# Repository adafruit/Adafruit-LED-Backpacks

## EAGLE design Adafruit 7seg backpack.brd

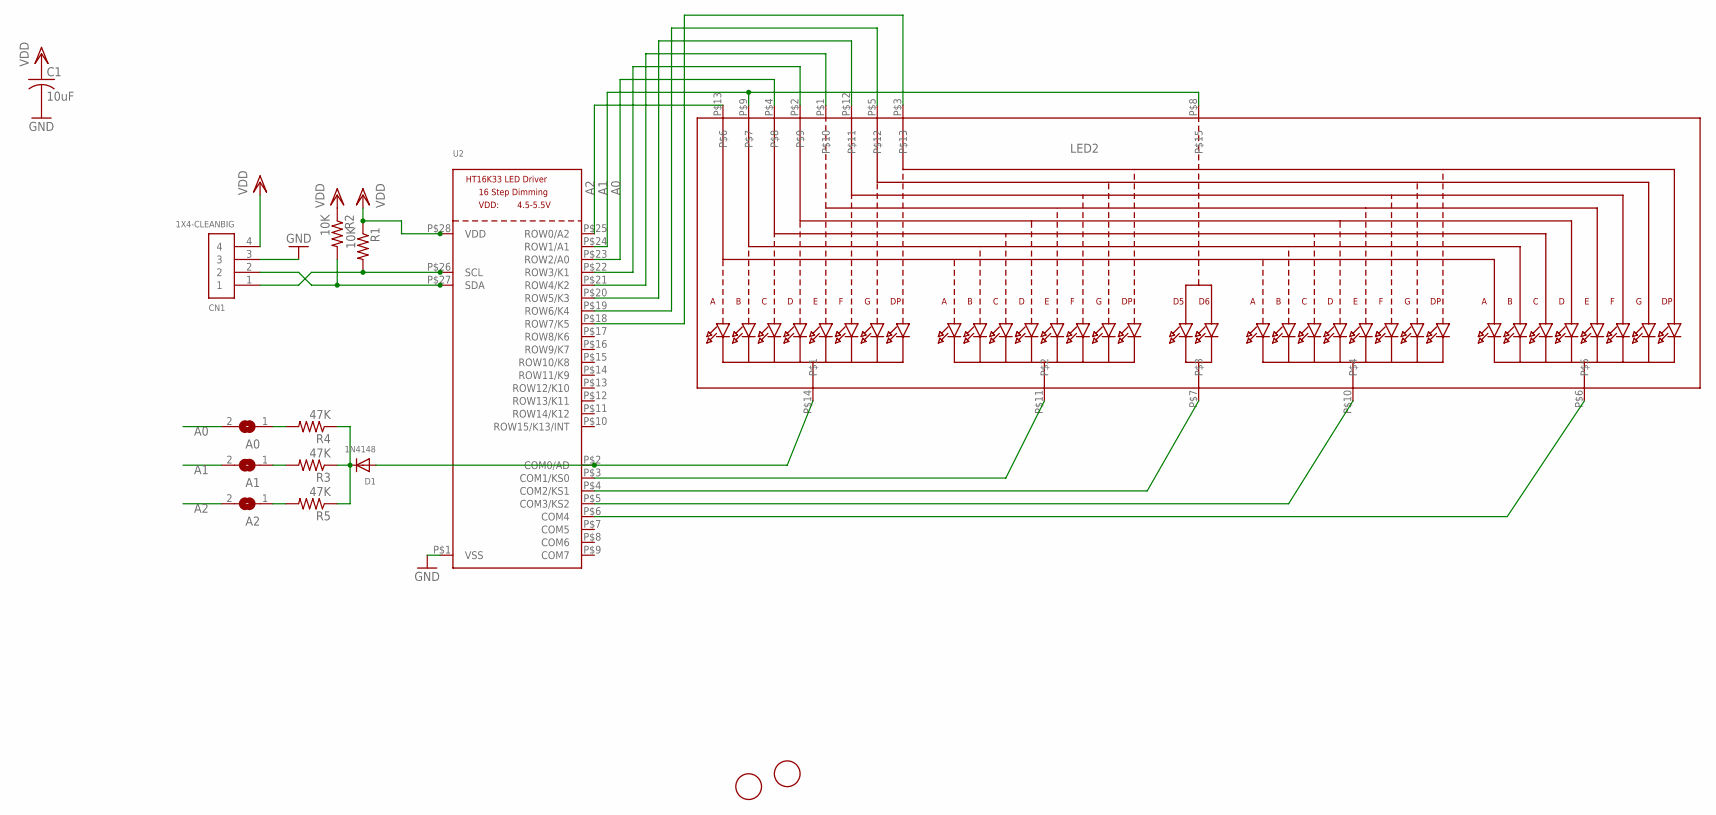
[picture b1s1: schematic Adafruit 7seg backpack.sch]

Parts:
A0, A1, A2: SOLDERJUMPERREFLOW_NOPASTE; SOLDERJUMPER_REFLOW_NOPASTE
C1: 10uF; C0805K
CN1: 1X4-CLEANBIG; 1X04-CLEANBIG
D1: 1N4148; SOD-323F
LED2: DISP_SEGMENT_4DIGIT_BL-Q56C43; SEGMENT-BL-Q56C43
R1, R2: 10K; R0805
R3, R4, R5: 47K; R0805
U2: HT16K33_SOP28; SOP28_300MIL
U$1, U$2: FIDUCIAL; FIDUCIAL_1MM

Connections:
A0: A0.2, LED2.P$4, U2.P$23 (ROW2/A0)
A1: A1.2, LED2.P$8, LED2.P$9, U2.P$24 (ROW1/A1)
A2: A2.2, LED2.P$13, U2.P$25 (ROW0/A2)
GND: C1.2, CN1.3, U2.P$1 (VSS)
unnamed: D1.C, R3.1, R4.1, R5.1
unnamed: D1.A, LED2.P$14, U2.P$2 (COM0/AD)
unnamed: LED2.P$11, U2.P$3 (COM1/KS0)
unnamed: LED2.P$7, U2.P$4 (COM2/KS1)
unnamed: LED2.P$10, U2.P$5 (COM3/KS2)
unnamed: LED2.P$6, U2.P$6 (COM4)
unnamed: A2.1, R5.2
unnamed: LED2.P$2, U2.P$22 (ROW3/K1)
unnamed: LED2.P$1, U2.P$21 (ROW4/K2)
unnamed: LED2.P$12, U2.P$20 (ROW5/K3)
unnamed: LED2.P$5, U2.P$19 (ROW6/K4)
unnamed: LED2.P$3, U2.P$18 (ROW7/K5)
unnamed: A1.1, R3.2
unnamed: A0.1, R4.2
SCL: CN1.1, R1.2, U2.P$26 (SCL)
SDA: CN1.2, R2.2, U2.P$27 (SDA)
VDD: C1.1, CN1.4, R1.1, R2.1, U2.P$28 (VDD)

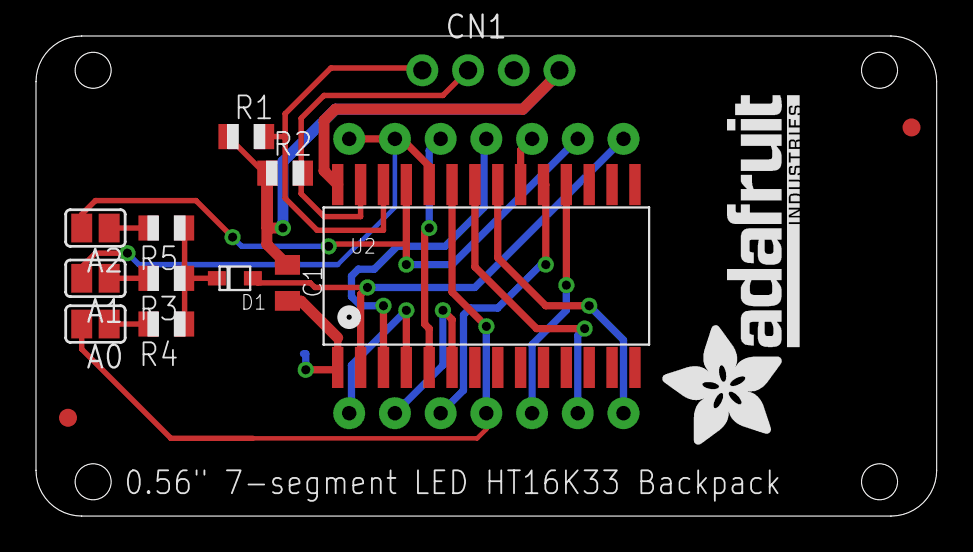
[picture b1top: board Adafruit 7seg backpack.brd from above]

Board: 2 copper layers, 50.0 x 26.7 mm, 16 parts (1 on the bottom side), 21 nets.

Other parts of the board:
U$3: ADAFRUIT_TEXT_20MM

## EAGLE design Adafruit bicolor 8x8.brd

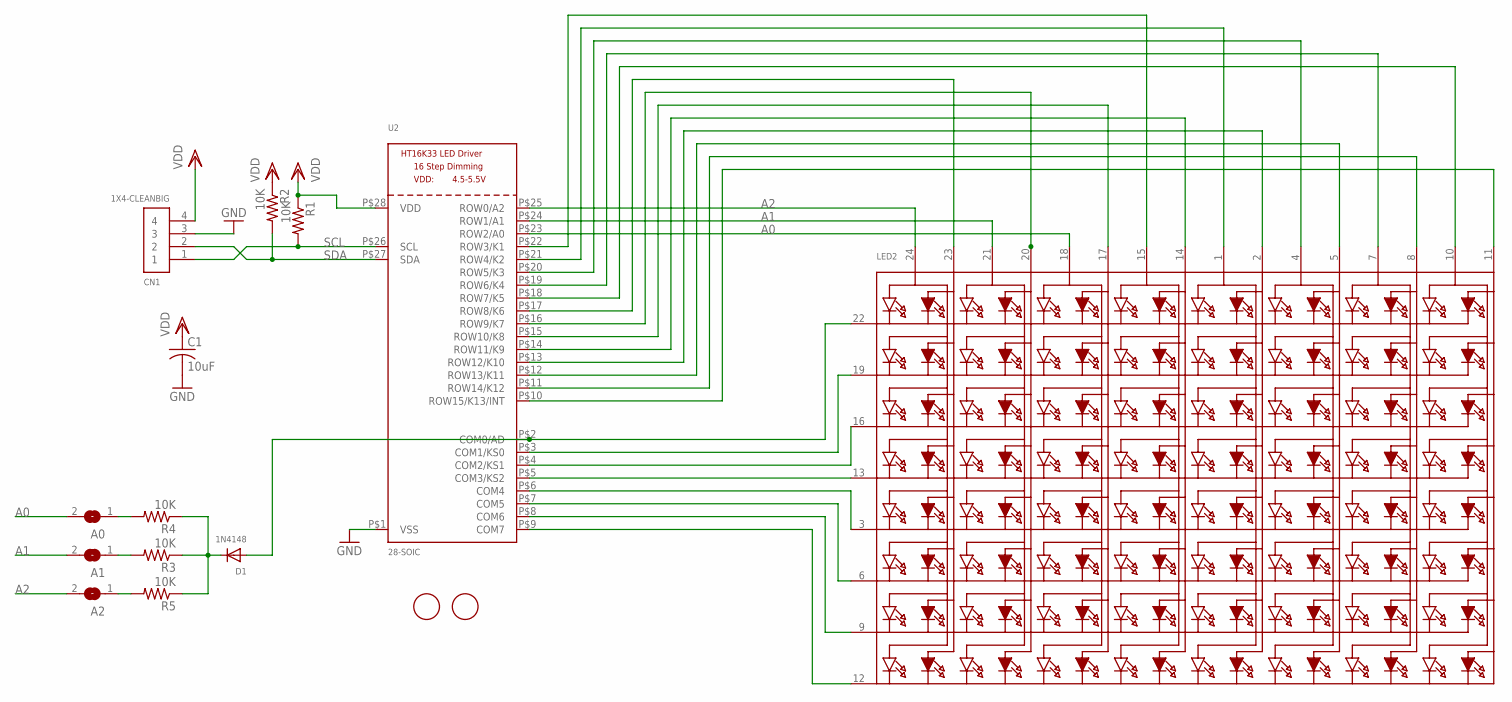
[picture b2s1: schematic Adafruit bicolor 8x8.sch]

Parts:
A0, A1, A2: SOLDERJUMPERREFLOW_NOPASTE; SOLDERJUMPER_REFLOW_NOPASTE
C1: 10uF; C0805
CN1: 1X4-CLEANBIG; 1X04-CLEANBIG
D1: 1N4148; SOD-323F
LED2: DISP_SEGMENT_8X8_BICOLOR_ROWCATHODEMI2A883XX; SEGMENT_BICOL_BL-M12A883XX
R1, R2, R3, R4, R5: 10K; R0805
U2: 28-SOIC; SOP28_300MIL
U$1, U$2: FIDUCIAL; FIDUCIAL_1MM

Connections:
A0: A0.2, LED2.18 (A5), U2.P$23 (ROW2/A0)
A1: A1.2, LED2.21 (A3), U2.P$24 (ROW1/A1)
A2: A2.2, LED2.24 (A1), U2.P$25 (ROW0/A2)
GND: C1.2, CN1.3, U2.P$1 (VSS)
unnamed: LED2.12 (K8), U2.P$9 (COM7)
unnamed: LED2.9 (K7), U2.P$8 (COM6)
unnamed: LED2.6 (K6), U2.P$7 (COM5)
unnamed: LED2.3 (K5), U2.P$6 (COM4)
unnamed: LED2.13 (K4), U2.P$5 (COM3/KS2)
unnamed: LED2.16 (K3), U2.P$4 (COM2/KS1)
unnamed: LED2.19 (K2), U2.P$3 (COM1/KS0)
unnamed: D1.A, LED2.22 (K1), U2.P$2 (COM0/AD)
unnamed: A2.1, R5.2
unnamed: LED2.8 (A14), U2.P$11 (ROW14/K12)
unnamed: LED2.5 (A12), U2.P$12 (ROW13/K11)
unnamed: LED2.11 (A16), U2.P$10 (ROW15/K13/INT)
unnamed: D1.C, R3.1, R4.1, R5.1
unnamed: A1.1, R3.2
unnamed: A0.1, R4.2
unnamed: LED2.10 (A15), U2.P$18 (ROW7/K5)
unnamed: LED2.7 (A13), U2.P$19 (ROW6/K4)
unnamed: LED2.1 (A9), U2.P$21 (ROW4/K2)
unnamed: LED2.15 (A7), U2.P$22 (ROW3/K1)
unnamed: LED2.4 (A11), U2.P$20 (ROW5/K3)
unnamed: LED2.23 (A2), U2.P$17 (ROW8/K6)
unnamed: LED2.20 (A4), U2.P$16 (ROW9/K7)
unnamed: LED2.14 (A8), U2.P$14 (ROW11/K9)
unnamed: LED2.17 (A6), U2.P$15 (ROW10/K8)
unnamed: LED2.2 (A10), U2.P$13 (ROW12/K10)
SCL: CN1.1, R1.2, U2.P$26 (SCL)
SDA: CN1.2, R2.2, U2.P$27 (SDA)
VDD: C1.1, CN1.4, R1.1, R2.1, U2.P$28 (VDD)

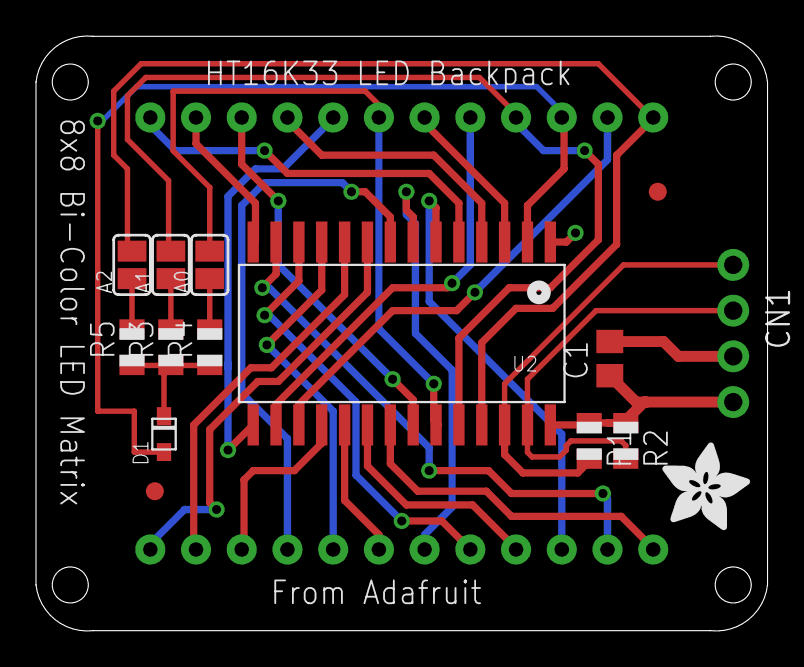
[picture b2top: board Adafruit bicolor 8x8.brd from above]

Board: 2 copper layers, 40.6 x 33.1 mm, 16 parts (1 on the bottom side), 32 nets.

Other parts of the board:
U$3: ADAFRUIT_5MM

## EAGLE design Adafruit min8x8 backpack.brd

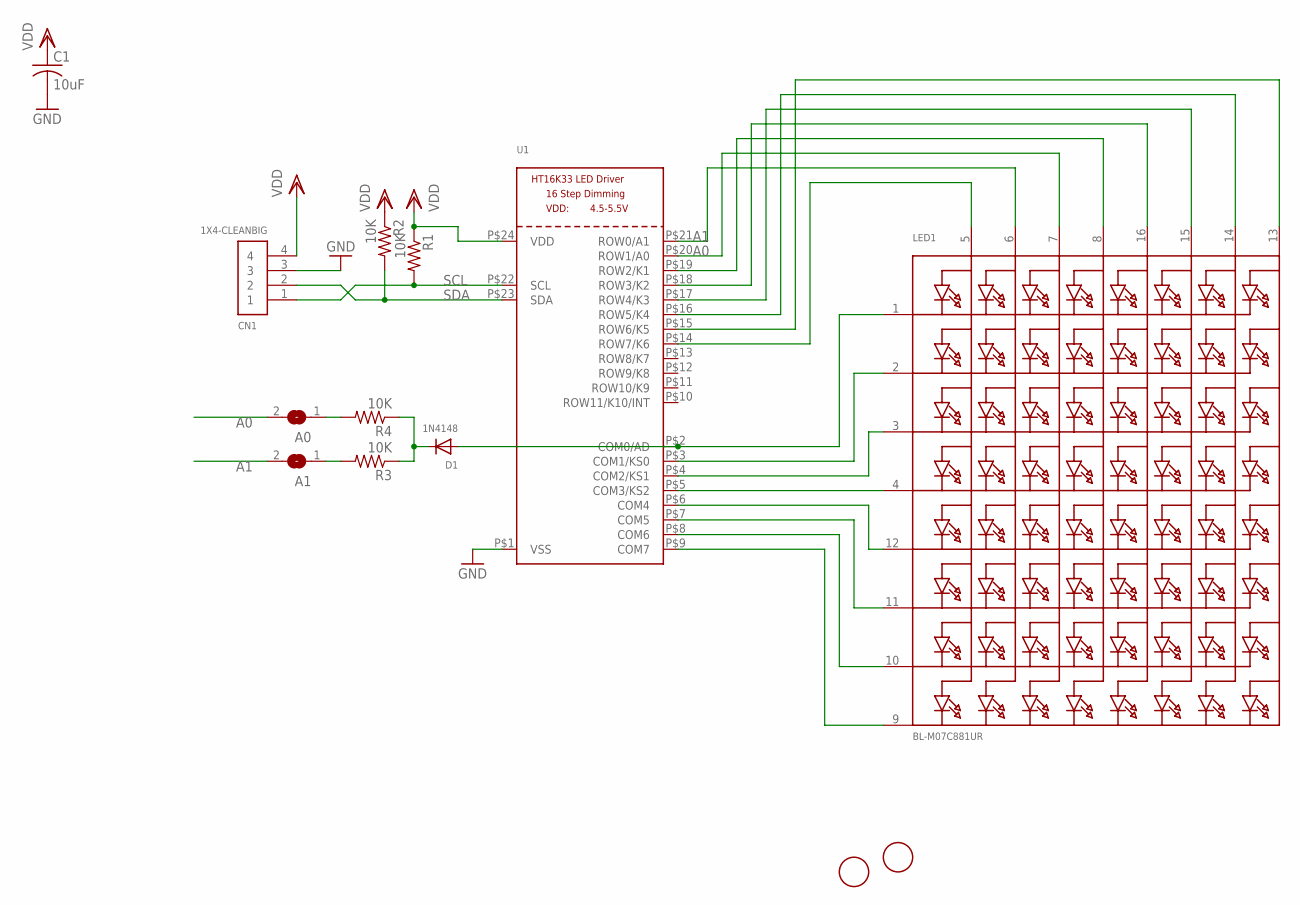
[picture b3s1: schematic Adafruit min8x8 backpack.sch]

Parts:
A0, A1: SOLDERJUMPERREFLOW_NOPASTE; SOLDERJUMPER_REFLOW_NOPASTE
C1: 10uF; C0805
CN1: 1X4-CLEANBIG; 1X04-CLEANBIG
D1: 1N4148; SOD-323F
LED1: BL-M07C881UR; SEGMENT_BL-M07C881UR
R1, R2, R3, R4: 10K; R0805
U1: HT16K33_SOP24; SOP24_300MIL
U$1, U$2: FIDUCIAL; FIDUCIAL_1MM

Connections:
A0: A0.2, LED1.7 (A3), U1.P$20 (ROW1/A0)
A1: A1.2, LED1.6 (A2), U1.P$21 (ROW0/A1)
GND: C1.2, CN1.3, U1.P$1 (VSS)
unnamed: LED1.9 (K8), U1.P$9 (COM7)
unnamed: LED1.10 (K7), U1.P$8 (COM6)
unnamed: LED1.11 (K6), U1.P$7 (COM5)
unnamed: LED1.12 (K5), U1.P$6 (COM4)
unnamed: LED1.4 (K4), U1.P$5 (COM3/KS2)
unnamed: LED1.3 (K3), U1.P$4 (COM2/KS1)
unnamed: LED1.2 (K2), U1.P$3 (COM1/KS0)
unnamed: D1.A, LED1.1 (K1), U1.P$2 (COM0/AD)
unnamed: LED1.8 (A4), U1.P$19 (ROW2/K1)
unnamed: LED1.16 (A5), U1.P$18 (ROW3/K2)
unnamed: LED1.15 (A6), U1.P$17 (ROW4/K3)
unnamed: D1.C, R3.1, R4.1
unnamed: LED1.5 (A1), U1.P$14 (ROW7/K6)
unnamed: A1.1, R3.2
unnamed: A0.1, R4.2
SCL: CN1.1, R1.2, U1.P$22 (SCL)
SDA: CN1.2, R2.2, U1.P$23 (SDA)
SEG_F: LED1.14 (A7), U1.P$16 (ROW5/K4)
SEG_G: LED1.13 (A8), U1.P$15 (ROW6/K5)
VDD: C1.1, CN1.4, R1.1, R2.1, U1.P$24 (VDD)

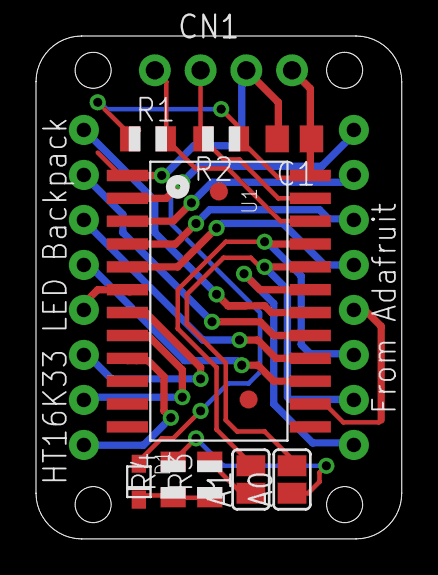
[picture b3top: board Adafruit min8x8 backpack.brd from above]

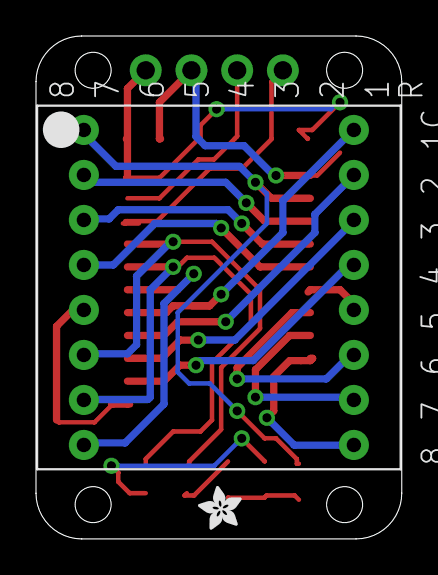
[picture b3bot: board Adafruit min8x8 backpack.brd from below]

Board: 2 copper layers, 20.3 x 27.9 mm, 14 parts (2 on the bottom side), 23 nets.

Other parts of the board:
U$4: ADAFRUIT_2.5MM
